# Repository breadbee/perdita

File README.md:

# Perdita

A tiny dual cortex A7 SBC you can make on your own clutter filled
messy desk!

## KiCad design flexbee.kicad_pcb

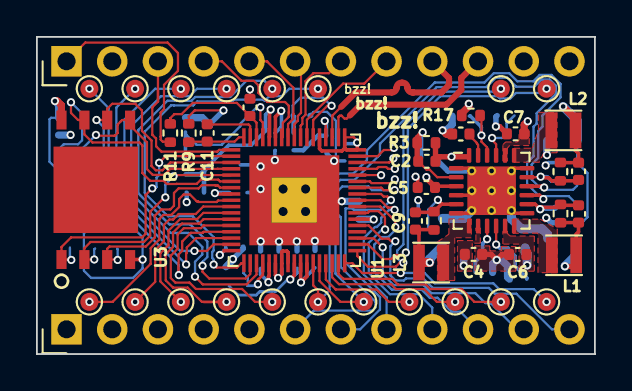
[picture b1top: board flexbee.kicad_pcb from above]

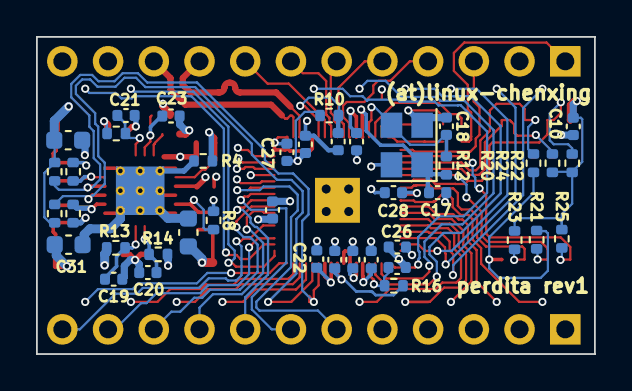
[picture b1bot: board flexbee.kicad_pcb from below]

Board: 4 copper layers, 31.0 x 17.6 mm, 86 parts (41 on the bottom side), 70 nets.

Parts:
C1, C2, C3, C4, C5, C6, C7, C8, C9, C10, C11, C12, C13, C14, C15, C16, C17, C18, C19, C20, C21, C22, C23, C24, C25, C26, C27, C28, C29, C30: C; C_0402_1005Metric
C31, C32, C33: C; C_0603_1608Metric
J1, J2: Conn_01x12_Male; PinHeader_1x12_P2.54mm_Vertical
L1, L2, L3: L; L_Taiyo-Yuden_MD-2020
R1, R2, R3, R4, R5, R6, R7, R8, R9, R10, R11, R12, R13, R14, R15, R16, R17, R18, R19, R20, R21, R22, R23, R24, R25: R; R_0402_1005Metric
TP1, TP2, TP3, TP4, TP5, TP6, TP7, TP8, TP9, TP10, TP11, TP12, TP13, TP14, TP15, TP16, TP17, TP18, TP19: TestPoint; TestPoint_Pad_D1.0mm
U1: SSD210; QFN-68_EP_7x7_Pitch0.35mm
U2: ea3056; QFN-24-1EP_4x4mm_P0.5mm_EP2.7x2.7mm_ThermalVias
U3: spinor; wson8-8x6mm
Y1: Crystal_GND24; Crystal_SMD_Abracon_ABM8G-4Pin_3.2x2.5mm

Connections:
+1V0: C1.1, C25.1, C27.1, C28.1, C31.1, L1.1, R1.1, R16.1, U1.8 (vdd), U1.26 (vdd), U1.51 (vdd), U1.52 (vdd), U1.56 (vdd)
+1V8: C9.1, C22.1, C24.1, C32.1, L3.2, R7.1, U1.23 (avddio_dram), U1.24 (vddio_data), U1.25 (avddio_dram), U1.27 (vddio_mclk), U1.28 (avddio_dram)
+3V3: C8.1, C10.1, C12.1, C14.1, C15.1, C26.1, C29.1, C30.1, C33.1, J1.1, L2.2, R5.1, R11.2, R18.1, R19.1, R22.2, R23.1, R24.1, R25.1, U1.17 (vddp1), U1.22 (avdd_pll), U1.40 (vddp2), U1.55 (avdd_usb), U1.63 (avdd_xtal), U3.8 (vdd)
/flash_clk: R20.1, U1.3 (pm_spi_ck), U3.6 (sck)
/flash_cs: R25.2, U1.2 (pm_spi_cz), U3.1 (~cs)
/flash_hld: R22.1, U1.6 (pm_spi_hld), U3.7 (~hold)
/flash_miso: R21.1, U1.5 (pm_spi_do), U3.2 (miso)
/flash_mosi: R24.2, U1.4 (pm_spi_di), U3.5 (mosi)
/flash_wpz: R23.2, U1.7 (pm_spi_wpz), U3.3 (~wp)
/i2c0_scl: R19.2, TP5.1, U1.29 (ttl0), U2.16 (SCL)
/i2c0_sda: R18.2, TP1.1, U1.30 (ttl1), U2.15 (SDA)
/lineout: J1.3, U1.1 (aud_lineout_l0)
/sar_gpio0: J1.4, U1.62 (sar_gpio0)
/sar_gpio1: J1.5, U1.61 (sar_gpio1)
/sar_gpio2: J1.6, U1.60 (sar_gpio2)
/ttl8: J2.11, U1.37 (ttl8)
/ttl11: J2.12, U1.39 (ttl11)
/ttl12: J2.9, U1.41 (ttl12)
/ttl13: J2.10, U1.42 (ttl13)
/ttl14: J2.8, U1.43 (ttl14)
/ttl15: J2.7, U1.44 (ttl15)
/ttl16: J2.6, U1.45 (ttl16)
/ttl17: J2.5, U1.46 (ttl17)
/ttl18: J2.4, U1.47 (ttl18)
/ttl19: J2.3, U1.48 (ttl19)
/ttl20: J2.2, U1.49 (ttl20)
/ttl21: J2.1, U1.50 (ttl21)
/uart_rx: J1.7, U1.59 (pm_uart_rx)
/uart_tx: J1.8, U1.58 (pm_uart_tx)
/usb+: J1.10, U1.53 (dp_p1)
/usb-: J1.9, U1.54 (dm_p1)
/xtal_in: C17.1, R12.1, U1.64 (xtal_in), Y1.1
/xtal_out: C18.1, R12.2, U1.65 (xtal_out), Y1.3
GND: C3.2, C4.2, C5.2, C6.2, C7.2, C10.2, C13.2, C14.2, C15.2, C16.2, C17.2, C18.2, C19.2, C20.2, C21.2, C22.2, C23.2, C24.2, C25.2, C26.2, C27.2, C28.2, C29.2, C30.2, C31.2, C32.2, C33.2, J1.2, R2.2, R4.2, R6.2, R8.2, R9.2, R10.2, R20.2, R21.2, U1.69 (GND), U2.1 (LDO_GND), U2.4 (AGND), U2.6 (GND2), U2.13 (GND1), U2.18 (GND3), U2.25 (GND), U3.4 (gnd), Y1.2, Y1.4
unnamed: C1.2, R1.2, R2.1, U2.14 (FB1)
unnamed: C2.2, R3.2, R4.1, U2.2 (LDO_FB)
unnamed: C3.1, U2.23 (LDO_I)
unnamed: C8.2, R5.2, R6.1, U2.17 (FB3)
unnamed: C9.2, R7.2, R8.1, U2.5 (FB2)
unnamed: C11.1, U1.67 (aud_vag)
unnamed: C11.2, R9.1, U1.68 (aud_vrm_dac)
unnamed: C12.2, R10.1, U1.57 (reset)
unnamed: C13.1, R11.1, U1.66 (avdd_aud)
unnamed: C16.1, R16.2, U1.21 (dvdd_ddr_rx)
unnamed: C19.1, R13.2, U2.10 (EN1)
unnamed: C20.1, R14.2, U2.9 (EN2)
unnamed: C21.1, R15.2, U2.21 (EN3)
unnamed: C23.1, R17.2, U2.22 (LDO_EN)
unnamed: L1.2, U2.12 (LX1)
unnamed: L2.1, U2.19 (LX3)
unnamed: L3.1, U2.7 (LX2)
unnamed: TP2.1, U1.31 (ttl2)
unnamed: TP3.1, U1.33 (ttl4)
unnamed: TP4.1, U1.35 (ttl6)
unnamed: TP6.1, U1.32 (ttl3)
unnamed: TP7.1, U1.34 (ttl5)
unnamed: TP8.1, U1.36 (ttl7)
unnamed: TP9.1, U1.9 (sr_io00)
unnamed: TP10.1, U1.11 (sr_io02)
unnamed: TP11.1, U1.13 (sr_io04)
unnamed: TP12.1, U1.15 (sr_io06)
unnamed: TP13.1, U1.18 (sr_io09)
unnamed: TP14.1, U1.20 (sr_io11)
unnamed: TP15.1, U1.10 (sr_io01)
unnamed: TP16.1, U1.12 (sr_io03)
unnamed: TP17.1, U1.14 (sr_io05)
unnamed: TP18.1, U1.16 (sr_io07)
unnamed: TP19.1, U1.19 (sr_io10)
VBUS: C2.1, J1.12, R3.1, U2.24 (LDO_O)
VCC: C4.1, C5.1, C6.1, C7.1, J1.11, R13.1, R14.1, R15.1, R17.1, U2.3 (VCC), U2.8 (VIN2), U2.11 (VIN1), U2.20 (VIN3)

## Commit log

2022-05-11 Stash
2022-05-12 Get rid of some junk..
2022-05-15 Layout work.
2022-06-01 test
2022-06-01 test2
2022-06-01 schematic check
2022-06-06 Create L_DND2020JE.STEP
    Added 3D model
2022-06-06 Added 3D models
2022-06-06 Finished laying you the board
2022-06-06 Layout Fixes
2022-06-06 Update boot resistors added
2022-06-06 Clean-up
2022-06-06 Silkscreen adjustment
2022-06-06 A few little touches
2022-09-05 Sync with my local machine
2023-03-05 Sync
2023-03-05 Add license. GPLv3 baby
2023-03-05 Add a photo
